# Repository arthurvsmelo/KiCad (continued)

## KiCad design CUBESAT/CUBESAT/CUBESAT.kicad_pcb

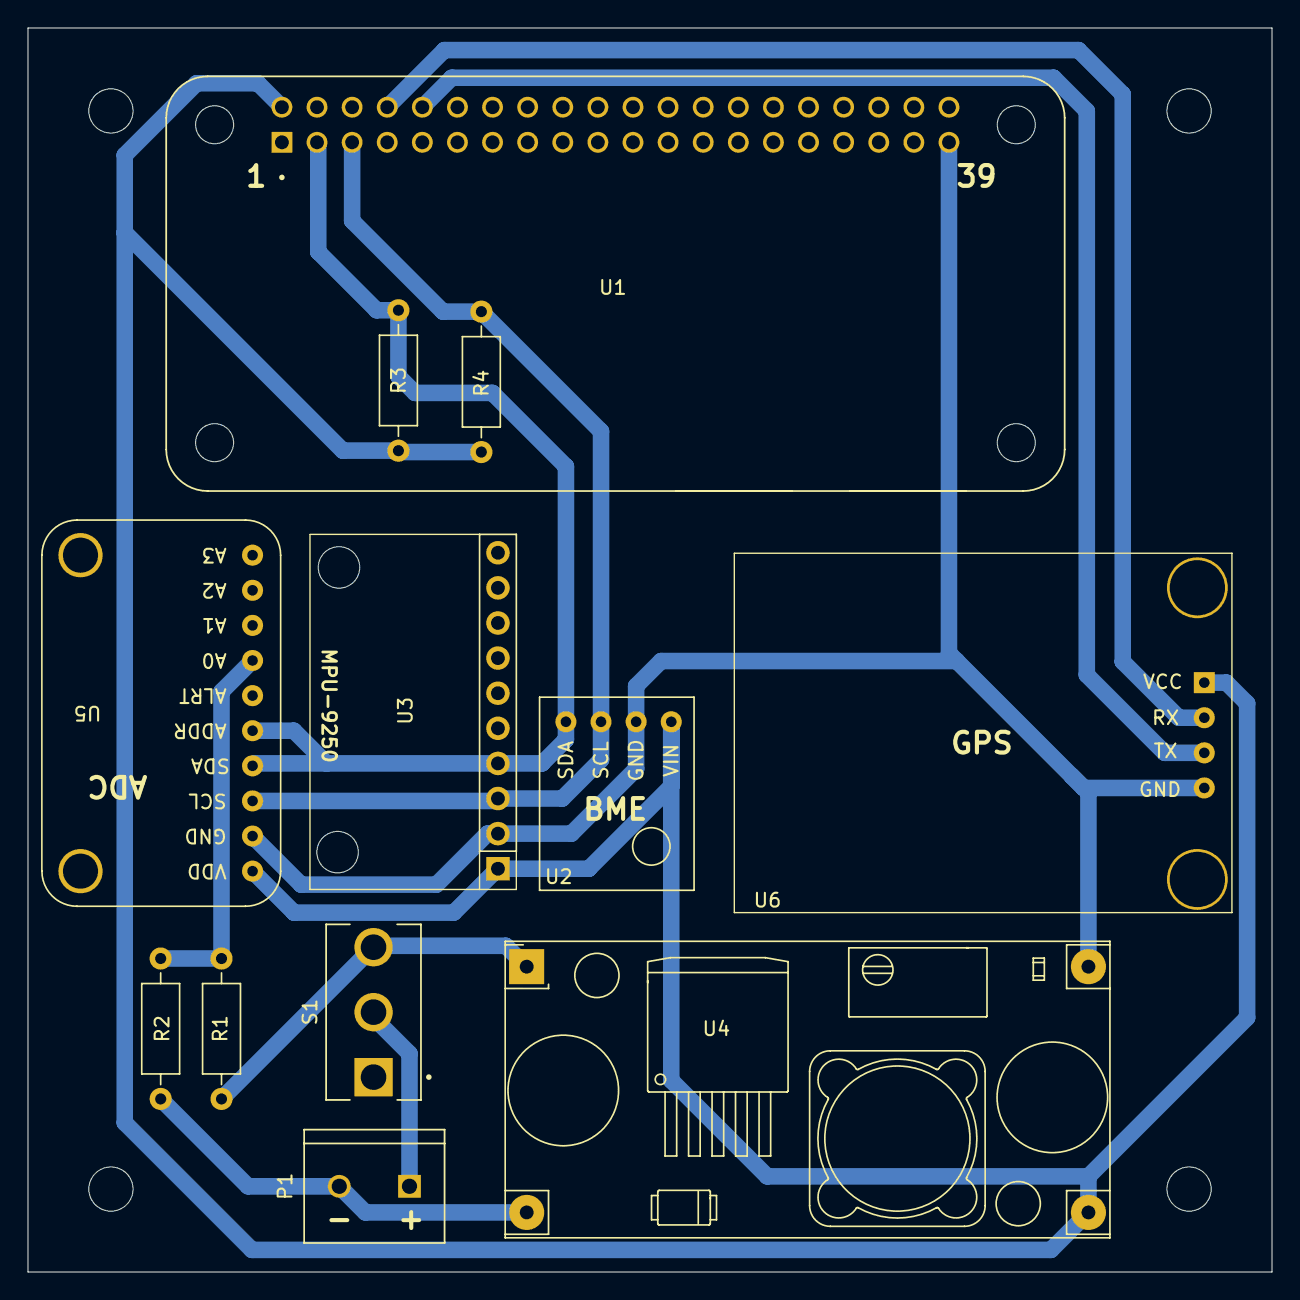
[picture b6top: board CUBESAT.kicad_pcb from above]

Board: 2 copper layers, 90.0 x 90.0 mm, 16 parts (0 on the bottom side), 10 nets.

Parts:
H1, H2, H3, H4: MountingHole; MountingHole_3.2mm_M3
P1: BORNE_KRE
R1, R2: 10k; R_Axial_DIN0207_L6.3mm_D2.5mm_P10.16mm_Horizontal
R3, R4: 4.8k; R_Axial_DIN0207_L6.3mm_D2.5mm_P10.16mm_Horizontal
S1: 100SP1T1B4M2QE; SW_100SP1T1B4M2QE
U1: MODULE_ADA3708; ADA3708
U2: BME280
U3: MPU9250
U4: YAAJ_DCDC_StepDown_LM2596
U5: Adafruit_ADS1115
U6: GY-NEO6MV2

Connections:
+5V: R3.1, R4.1, U1.2 (5V_1), U2.1 (VIN), U3.1 (VCC), U4.3 (OUT+), U5.1 (VDD), U6.1 (VCC)
/ADC_IN: R1.2, R2.1, U5.7 (A0)
/RXD0_GPIO15: U1.10 (RXD0_GPIO15), U6.3 (TX)
/SCL: R4.2, U1.5 (GPIO3_SCL), U2.3 (SCL), U3.3 (SCL), U5.3 (I2C_SCL)
/SDA: R3.2, U1.3 (GPIO2_SDA), U2.4 (SDA), U3.4 (SDA), U5.4 (I2C_SDA), U5.5 (ADDR)
/TXD0_GPIO14: U1.8 (TXD0_GPIO14), U6.2 (RX)
GND: U1.39 (GND_3), U2.2 (GND), U3.2 (GND), U4.4 (OUT-), U5.2 (GND), U6.4 (GND)
unnamed: P1.1, S1.2
unnamed: R1.1, S1.3, U4.1 (IN+)
unnamed: P1.2, R2.2, U4.2 (IN-)

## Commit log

2024-07-11 create repository / initial commit
2024-07-18 pcb finished
2024-08-22 add teste_estatico project
2024-09-02 create harpia2 project folder
2024-09-11 layout changes in harpia PCB
2024-09-14 esquematico da carga eletronica
2024-09-20 create squib trigger circuit diagram
